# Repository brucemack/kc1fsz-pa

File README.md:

References
==========

A useful document for designing with PIN diodes: https://cdn.macom.com/applicationnotes/AG312.pdf

PIN diode: https://www.digikey.com/en/products/detail/nxp-usa-inc/BAP51-02-115/807435

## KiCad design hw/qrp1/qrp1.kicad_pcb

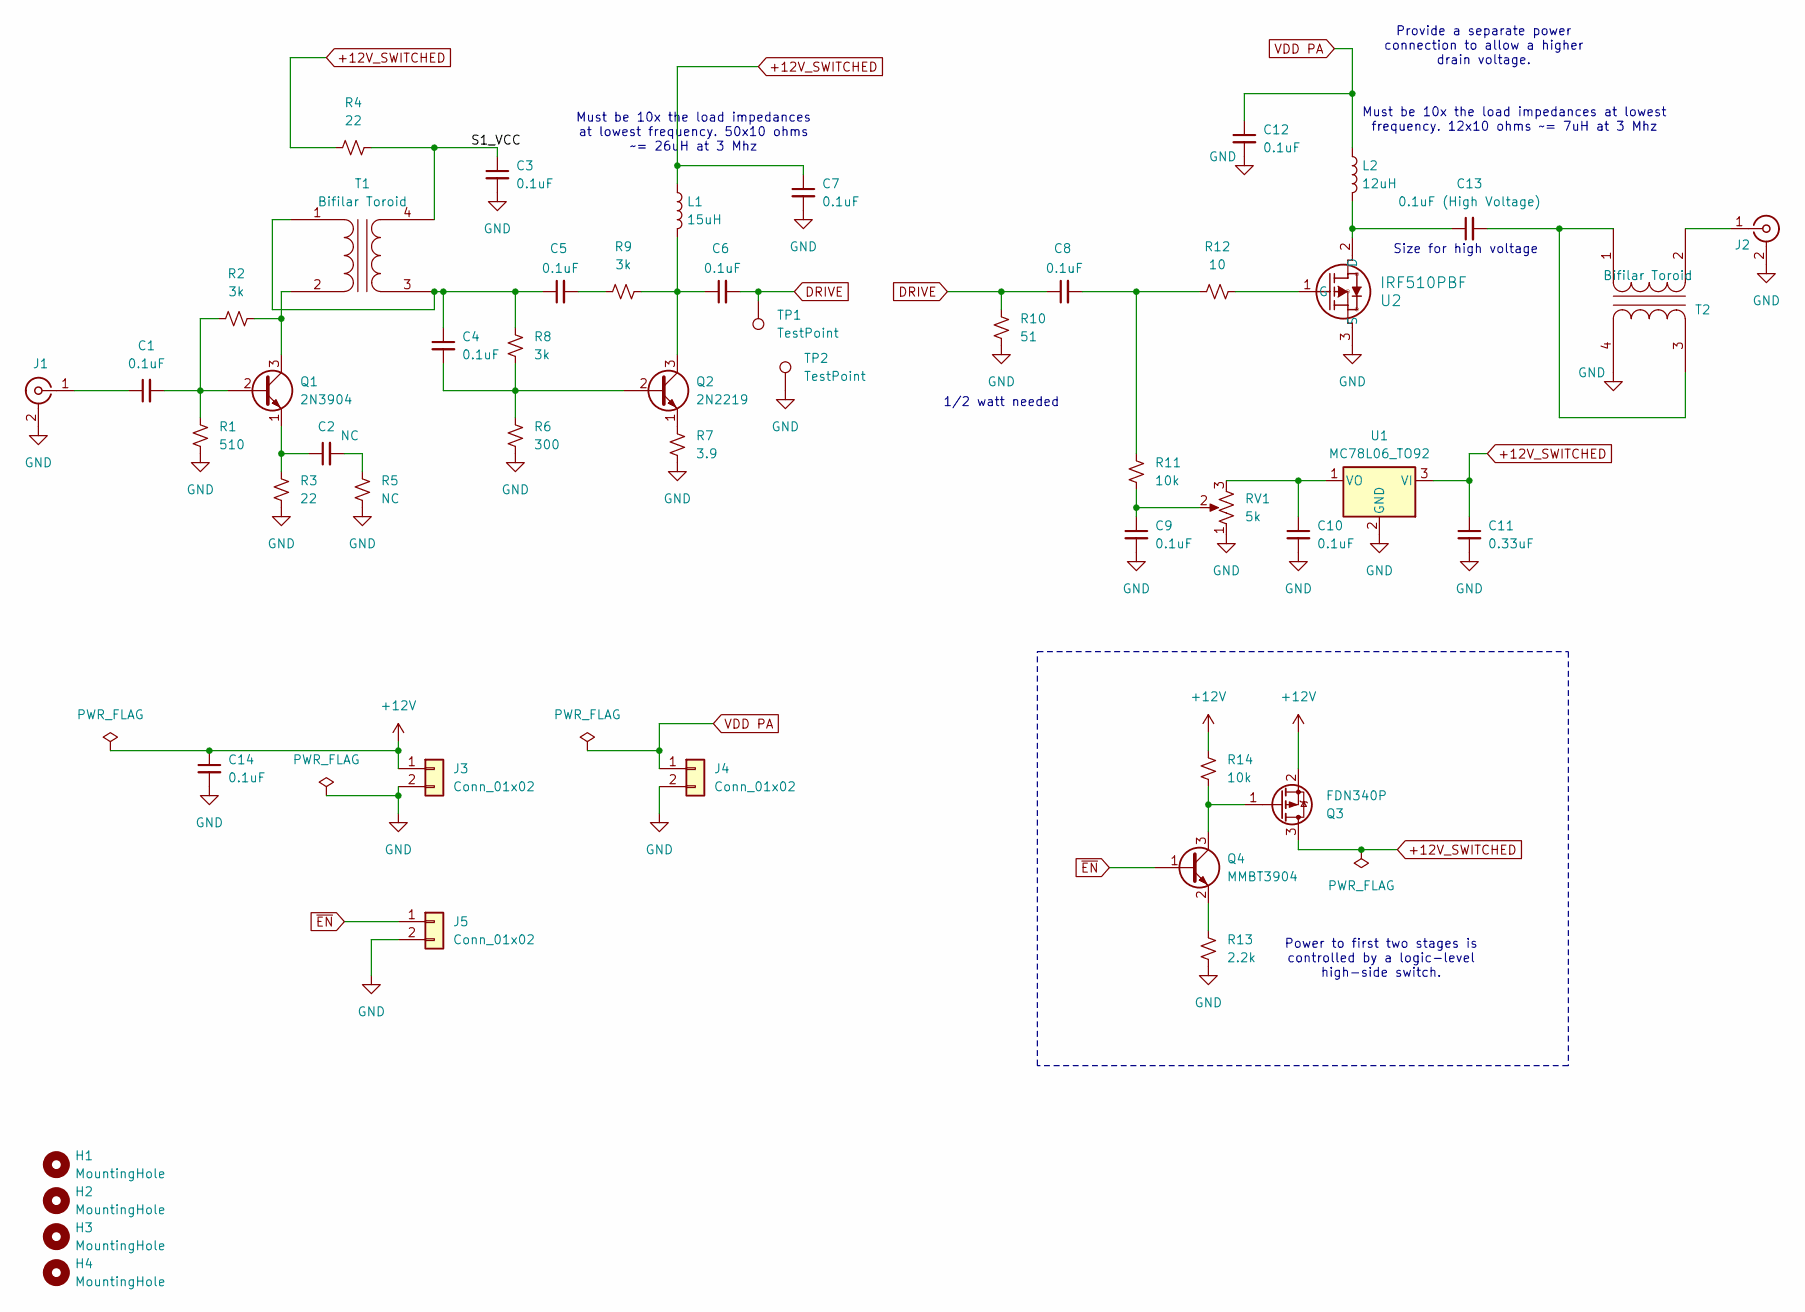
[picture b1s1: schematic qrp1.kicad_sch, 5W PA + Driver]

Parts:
C1, C3, C4, C5, C6, C7, C8, C9, C10, C12, C14: 0.1uF; C_0805_2012Metric_Pad1.18x1.45mm_HandSolder
C2: NC; C_0805_2012Metric_Pad1.18x1.45mm_HandSolder
C11: 0.33uF; C_0805_2012Metric_Pad1.18x1.45mm_HandSolder
C13: 0.1uF (High Voltage); C_0805_2012Metric_Pad1.18x1.45mm_HandSolder
H1, H2, H3, H4: MountingHole; MountingHole_3.5mm
J1, J2: Conn_Coaxial; SMA_Amphenol_901-144_Vertical
J3, J4, J5: Conn_01x02; PinHeader_1x02_P2.54mm_Vertical
L1: 15uH; L_Toroid_Horizontal_D9.5mm_P15.00mm_Diameter10-5mm_Amidon-T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
L2: 12uH; L_Toroid_Horizontal_D9.5mm_P15.00mm_Diameter10-5mm_Amidon-T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
Q1: 2N3904; TO-92_Inline
Q2: 2N2219; TO-39-3
Q3: FDN340P; SOT-23
Q4: MMBT3904; SOT-23
R1: 510; R_0805_2012Metric_Pad1.20x1.40mm_HandSolder
R2, R8, R9: 3k; R_0805_2012Metric_Pad1.20x1.40mm_HandSolder
R3, R4: 22; R_0805_2012Metric_Pad1.20x1.40mm_HandSolder
R5: NC; R_0805_2012Metric_Pad1.20x1.40mm_HandSolder
R6: 300; R_0805_2012Metric_Pad1.20x1.40mm_HandSolder
R7: 3.9; R_0805_2012Metric_Pad1.20x1.40mm_HandSolder
R10: 51; R_Axial_DIN0309_L9.0mm_D3.2mm_P5.08mm_Vertical
R11, R14: 10k; R_0805_2012Metric_Pad1.20x1.40mm_HandSolder
R12: 10; R_0805_2012Metric_Pad1.20x1.40mm_HandSolder
R13: 2.2k; R_0805_2012Metric_Pad1.20x1.40mm_HandSolder
RV1: 5k; POT_3362P
T1, T2: Bifilar Toroid; FT37-43 Bifilar
TP1, TP2: TestPoint; TestPoint_Pad_1.5x1.5mm
U1: MC78L06_TO92; TO-92_Inline
U2: IRF510PBF; TO-220-3_Vertical

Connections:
+12V: C14.1, J3.1, Q3.2 (S), R14.1
+12V_SWITCHED: C7.1, C11.1, L1.1, Q3.3 (D), R4.1, U1.3 (VI)
/S1_VCC: C3.1, R4.2, T1.4 (SB)
DRIVE: C6.2, C8.1, R10.1, TP1.1
GND: C3.2, C7.2, C9.2, C10.2, C11.2, C12.2, C14.2, J1.2 (Ext), J2.2 (Ext), J3.2, J4.2, J5.2, R1.2, R3.2, R5.2, R6.2, R7.2, R10.2, R13.2, RV1.1, T2.4 (SB), TP2.1, U1.2 (GND), U2.3 (S)
unnamed: C2.2, R5.1
unnamed: C5.2, R9.1
unnamed: C8.2, R11.1, R12.1
unnamed: C9.1, R11.2, RV1.2
unnamed: C1.1, J1.1 (In)
unnamed: J2.1 (In), T2.2 (AB)
unnamed: C1.2, Q1.2 (B), R1.1, R2.1
unnamed: Q1.3 (C), R2.2, T1.2 (AB)
unnamed: C2.1, Q1.1 (E), R3.1
unnamed: C4.2, Q2.2 (B), R6.1, R8.2
unnamed: C6.1, L1.2, Q2.3 (C), R9.2
unnamed: Q2.1 (E), R7.1
unnamed: Q3.1 (G), Q4.3 (C), R14.2
unnamed: Q4.2 (E), R13.1
unnamed: C4.1, C5.1, R8.1, T1.1 (AA), T1.3 (SA)
unnamed: C13.2, T2.1 (AA), T2.3 (SA)
unnamed: C10.1, RV1.3, U1.1 (VO)
unnamed: C13.1, L2.2, U2.2 (D)
unnamed: R12.2, U2.1 (G)
VDD PA: C12.1, J4.1, L2.1
~EN: J5.1, Q4.1 (B)

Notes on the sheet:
Must be 10x the load impedances at lowest frequency. 12x10 ohms ~= 7uH at 3 Mhz
Provide a separate power connection to allow a higher drain voltage.
Power to first two stages is controlled by a logic-level high-side switch.
Must be 10x the load impedances at lowest frequency. 50x10 ohms ~= 26uH at 3 Mhz
Size for high voltage
1/2 watt needed

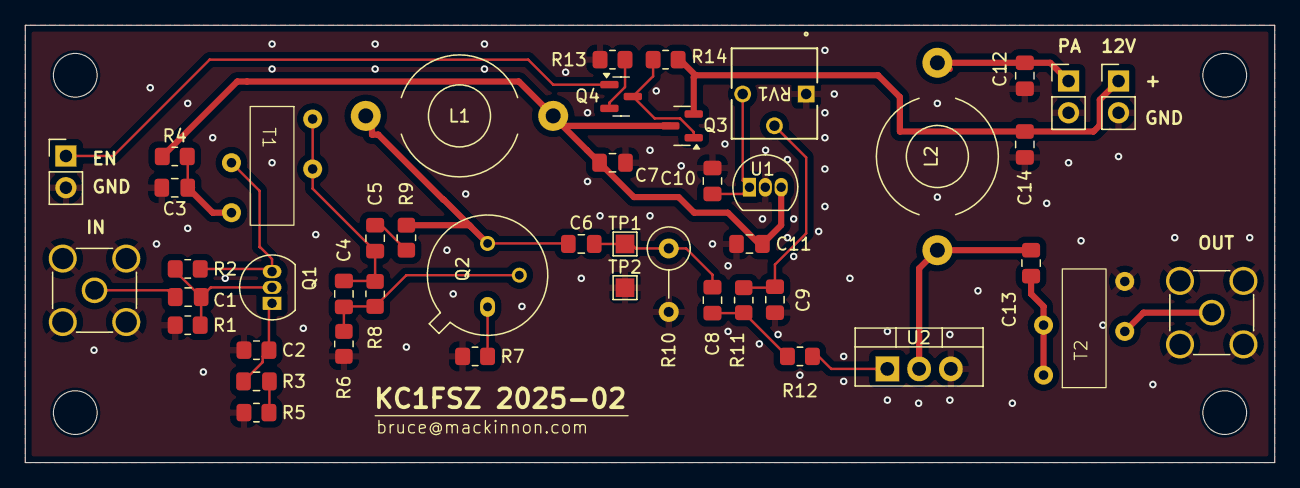
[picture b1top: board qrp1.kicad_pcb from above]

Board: 2 copper layers, 100.0 x 35.0 mm, 50 parts (0 on the bottom side), 26 nets.

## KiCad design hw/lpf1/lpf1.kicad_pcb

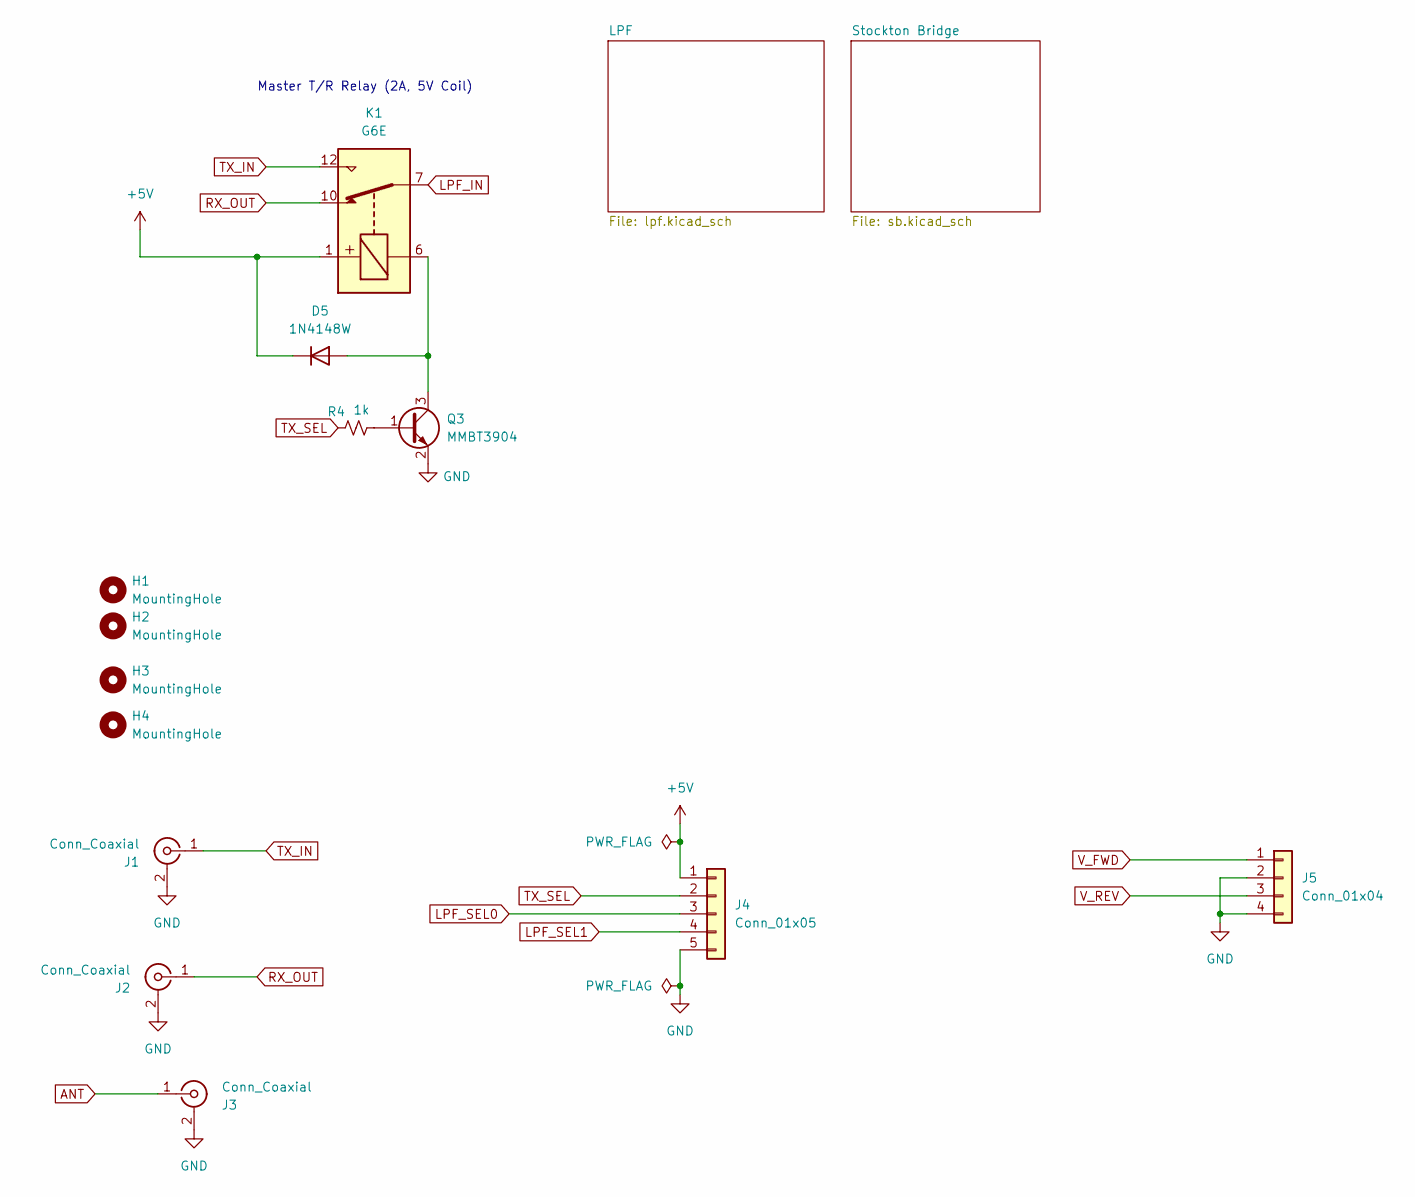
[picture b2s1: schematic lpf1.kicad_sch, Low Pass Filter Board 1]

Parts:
D5: 1N4148W; D_SOD-123
H1, H2, H3, H4: MountingHole; MountingHole_3.5mm
J1, J2, J3: Conn_Coaxial; SMA_Amphenol_901-144_Vertical
J4: Conn_01x05; PinHeader_1x05_P2.54mm_Vertical
J5: Conn_01x04; PinHeader_1x04_P2.54mm_Vertical
K1: G6E; Relay_SPDT_Omron_G6E
Q3: MMBT3904; SOT-23
R4: 1k; R_0805_2012Metric_Pad1.20x1.40mm_HandSolder

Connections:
+5V: D5.1 (K), J4.1, K1.1; also elsewhere on the board
ANT: J3.1 (In); also elsewhere on the board
GND: J1.2 (Ext), J2.2 (Ext), J3.2 (Ext), J4.5, J5.2, J5.4, Q3.2 (E); also elsewhere on the board
LPF_IN: K1.7; also elsewhere on the board
LPF_SEL0: J4.3; also elsewhere on the board
LPF_SEL1: J4.4; also elsewhere on the board
unnamed: D5.2 (A), K1.6, Q3.3 (C)
unnamed: Q3.1 (B), R4.2
RX_OUT: J2.1 (In), K1.10
TX_IN: J1.1 (In), K1.12
TX_SEL: J4.2, R4.1
V_FWD: J5.1; also elsewhere on the board
V_REV: J5.3; also elsewhere on the board

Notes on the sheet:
Master T/R Relay (2A, 5V Coil)

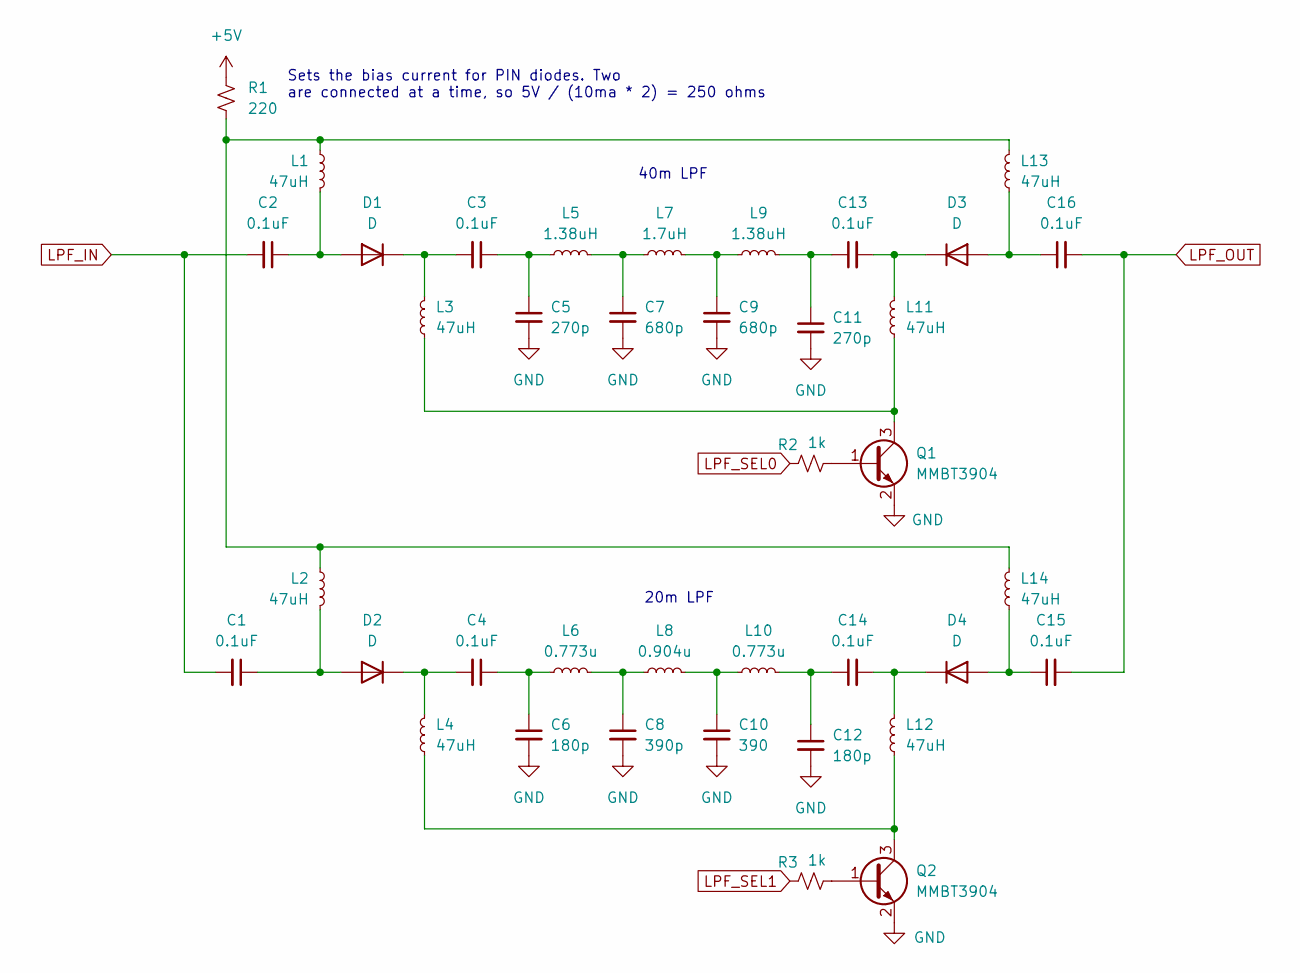
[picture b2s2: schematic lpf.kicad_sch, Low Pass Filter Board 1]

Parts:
C1, C2, C3, C4, C13, C14, C15, C16: 0.1uF; C_0805_2012Metric_Pad1.18x1.45mm_HandSolder
C5, C11: 270p; C_0805_2012Metric_Pad1.18x1.45mm_HandSolder
C6, C12: 180p; C_0805_2012Metric_Pad1.18x1.45mm_HandSolder
C7, C9: 680p; C_0805_2012Metric_Pad1.18x1.45mm_HandSolder
C8: 390p; C_0805_2012Metric_Pad1.18x1.45mm_HandSolder
C10: 390; C_0805_2012Metric_Pad1.18x1.45mm_HandSolder
D1, D2, D3, D4: D; D_SOD-523
L1, L2, L3, L4, L11, L12, L13, L14: 47uH; L_0805_2012Metric_Pad1.15x1.40mm_HandSolder
L5, L9: 1.38uH; FT37-43 Unifilar
L6, L10: 0.773u; FT37-43 Unifilar
L7: 1.7uH; FT37-43 Unifilar
L8: 0.904u; FT37-43 Unifilar
Q1, Q2: MMBT3904; SOT-23
R1: 220; R_0805_2012Metric_Pad1.20x1.40mm_HandSolder
R2, R3: 1k; R_0805_2012Metric_Pad1.20x1.40mm_HandSolder

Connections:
+5V: R1.1; also elsewhere on the board
GND: C5.2, C6.2, C7.2, C8.2, C9.2, C10.2, C11.2, C12.2, Q1.2 (E), Q2.2 (E); also elsewhere on the board
LPF_IN: C1.2, C2.2; also elsewhere on the board
LPF_OUT: C15.2, C16.2; also elsewhere on the board
LPF_SEL0: R2.1; also elsewhere on the board
LPF_SEL1: R3.1; also elsewhere on the board
unnamed: C3.1, C5.1, L5.1
unnamed: C4.1, C6.1, L6.1
unnamed: C7.1, L5.2, L7.1
unnamed: C8.1, L6.2, L8.1
unnamed: C9.1, L7.2, L9.1
unnamed: C10.1, L8.2, L10.1
unnamed: C11.1, C13.1, L9.2
unnamed: C12.1, C14.1, L10.2
unnamed: C2.1, D1.2 (A), L1.1
unnamed: C3.2, D1.1 (K), L3.2
unnamed: C1.1, D2.2 (A), L2.1
unnamed: C4.2, D2.1 (K), L4.2
unnamed: C16.1, D3.2 (A), L13.1
unnamed: C13.2, D3.1 (K), L11.2
unnamed: C15.1, D4.2 (A), L14.1
unnamed: C14.2, D4.1 (K), L12.2
unnamed: L1.2, L2.2, L13.2, L14.2, R1.2
unnamed: Q1.1 (B), R2.2
unnamed: L3.1, L11.1, Q1.3 (C)
unnamed: Q2.1 (B), R3.2
unnamed: L4.1, L12.1, Q2.3 (C)

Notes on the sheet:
40m LPF
Sets the bias current for PIN diodes. Two are connected at a time, so 5V / (10ma * 2) = 250 ohms
20m LPF

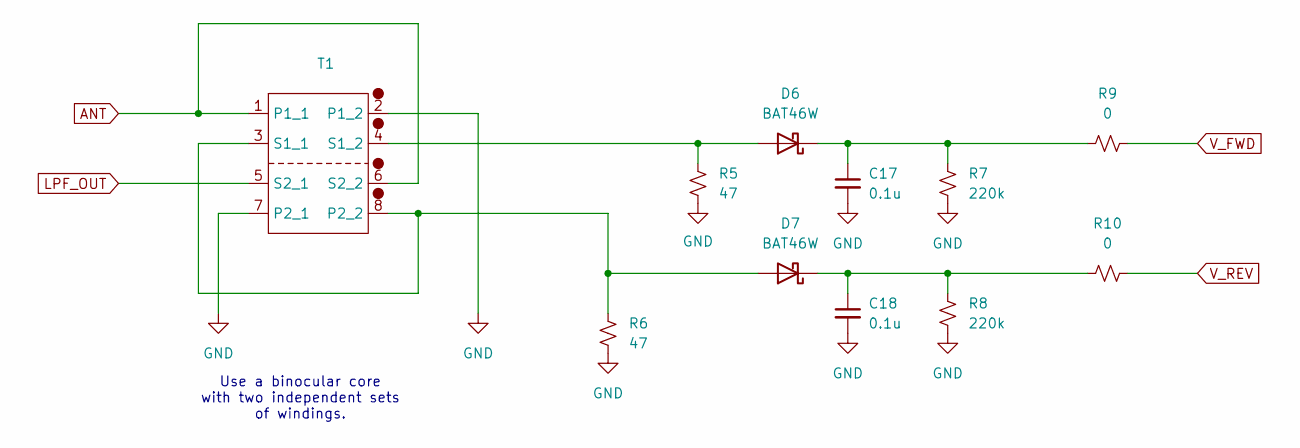
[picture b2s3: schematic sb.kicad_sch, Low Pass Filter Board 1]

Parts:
C17, C18: 0.1u; C_0805_2012Metric_Pad1.18x1.45mm_HandSolder
D6, D7: BAT46W; D_SOD-123
R5, R6: 47; R_0805_2012Metric_Pad1.20x1.40mm_HandSolder
R7, R8: 220k; R_0805_2012Metric_Pad1.20x1.40mm_HandSolder
R9, R10: 0; R_0805_2012Metric_Pad1.20x1.40mm_HandSolder
T1: Dual Transformer 1

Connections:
ANT: T1.1 (P1_1), T1.6 (S2_2); also elsewhere on the board
GND: C17.2, C18.2, R5.2, R6.2, R7.2, R8.2, T1.2 (P1_2), T1.7 (P2_1); also elsewhere on the board
LPF_OUT: T1.5 (S2_1); also elsewhere on the board
unnamed: D6.2 (A), R5.1, T1.4 (S1_2)
unnamed: C17.1, D6.1 (K), R7.1, R9.1
unnamed: D7.2 (A), R6.1, T1.3 (S1_1), T1.8 (P2_2)
unnamed: C18.1, D7.1 (K), R8.1, R10.1
V_FWD: R9.2; also elsewhere on the board
V_REV: R10.2; also elsewhere on the board

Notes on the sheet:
Use a binocular core with two independent sets of windings.

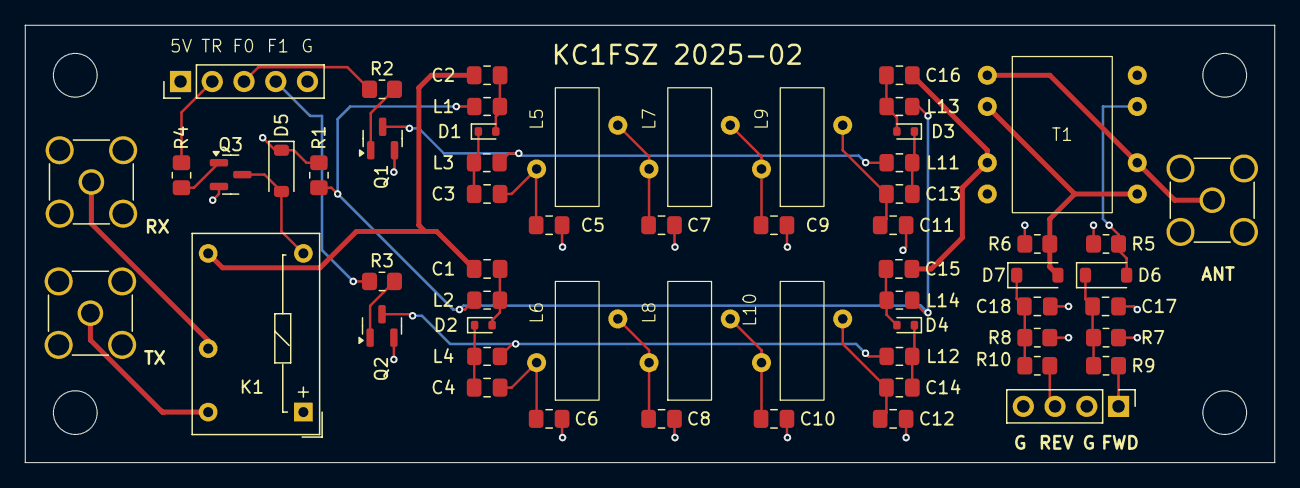
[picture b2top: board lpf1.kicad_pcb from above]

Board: 4 copper layers, 100.0 x 35.0 mm, 63 parts (0 on the bottom side), 39 nets.

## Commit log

2025-02-19 Initital commit
2025-02-20 Added power enable control on driver stages
2025-02-21 Layout in process
2025-02-21 Layout complete
2025-02-21 Ready to sent to fab
2025-02-21 Sending QRP PA/LPF boards to JLC

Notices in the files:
hw/lpf1/lpf.kicad_sch:
Copyright (C) Bruce MacKinnon, 2025
